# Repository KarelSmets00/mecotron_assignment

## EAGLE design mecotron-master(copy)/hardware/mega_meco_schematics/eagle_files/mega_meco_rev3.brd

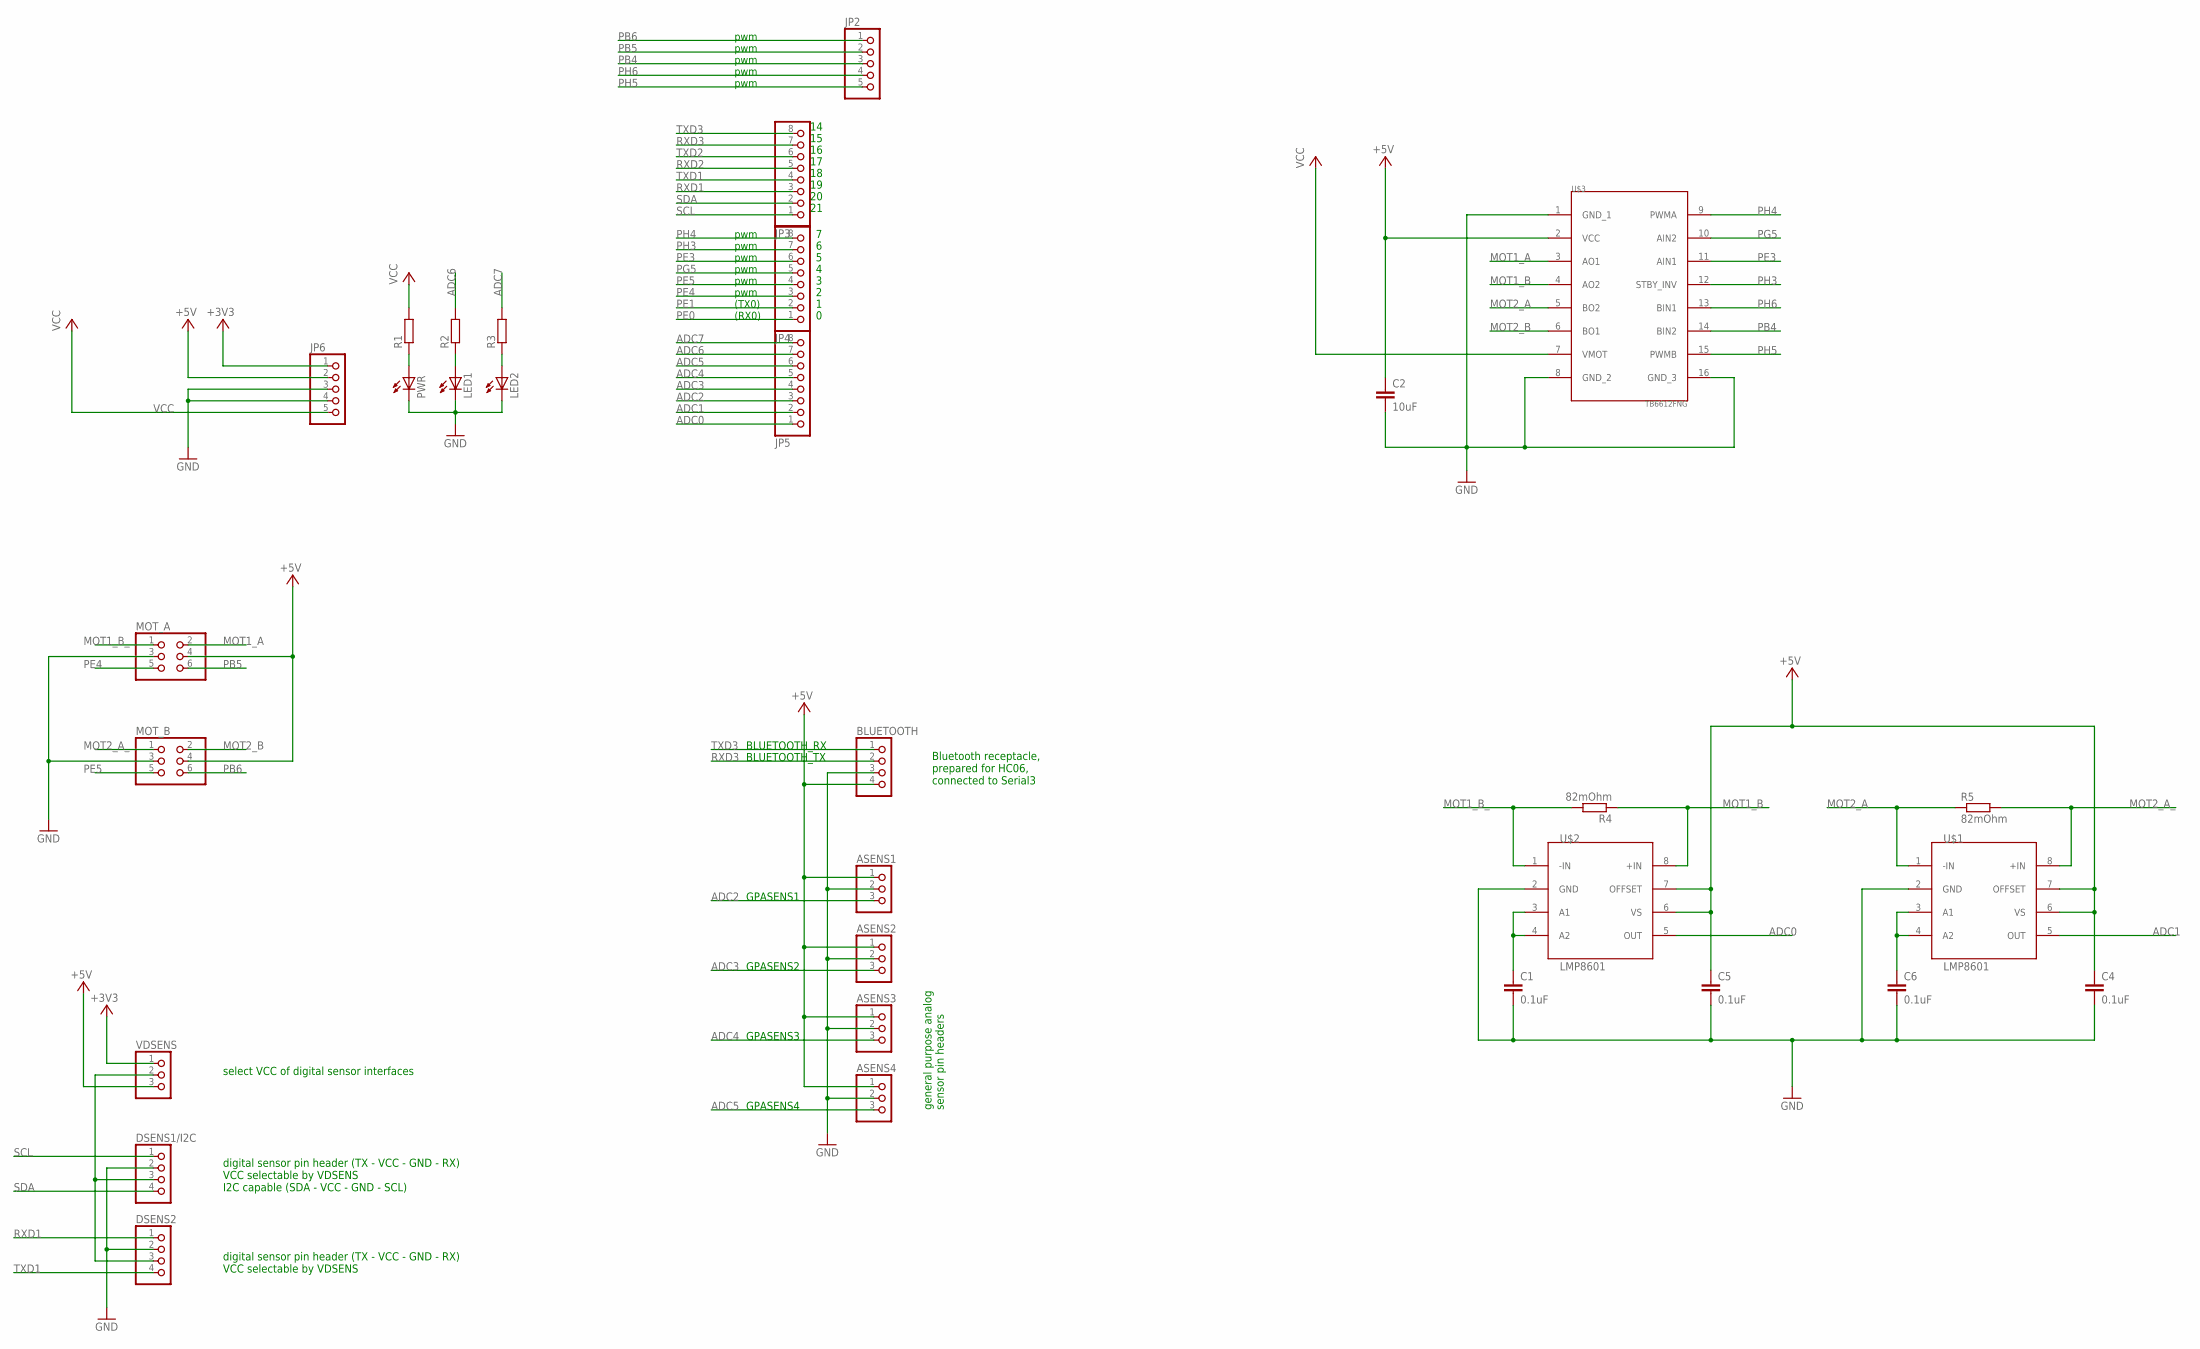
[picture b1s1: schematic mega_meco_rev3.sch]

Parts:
ASENS1, ASENS2, ASENS3, ASENS4: PINHD-1X3; 1X03
BLUETOOTH: PINHD-1X4; 1X04
C1, C4, C5, C6: 0.1uF; C0805
C2: 10uF; C1206
DSENS1/I2C, DSENS2: PINHD-1X4; 1X04
JP2, JP6: PINHD-1X5; 1X05
JP3, JP4, JP5: PINHD-1X8; 1X08
LED1, LED2: LED3MM
MOT_A: PINHD-2X3; 2X03
MOT_B: PINHD-2X3; 2X03
PWR: LED5MM
R1, R2, R3: R-EU_R0805; R0805
R4, R5: 82mOhm; R1206
U$1, U$2: LMP8601; SOIC127P600X175-8N
U$3: TB6612FNG; TB6612FNG_CARRIER
VDSENS: PINHD-1X3; 1X03

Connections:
+3V3: JP6.1, VDSENS.1
+5V: ASENS1.1, ASENS2.1, ASENS3.1, ASENS4.1, BLUETOOTH.4, C2.1, C4.1, C5.1, JP6.2, MOT_A.4, MOT_B.4, U$1.6 (VS), U$1.7 (OFFSET), U$2.6 (VS), U$2.7 (OFFSET), U$3.2 (VCC), VDSENS.3
ADC0: JP5.1, U$2.5 (OUT)
ADC1: JP5.2, U$1.5 (OUT)
ADC2: ASENS1.3, JP5.3
ADC3: ASENS2.3, JP5.4
ADC4: ASENS3.3, JP5.5
ADC5: ASENS4.3, JP5.6
ADC6: JP5.7, R2.2
ADC7: JP5.8, R3.2
GND: ASENS1.2, ASENS2.2, ASENS3.2, ASENS4.2, BLUETOOTH.3, C1.2, C2.2, C4.2, C5.2, C6.2, DSENS1/I2C.2, DSENS2.2, JP6.3, JP6.4, LED1.K (C), LED2.K (C), MOT_A.3, MOT_B.3, PWR.K (C), U$1.2 (GND), U$2.2 (GND), U$3.1 (GND_1), U$3.8 (GND_2), U$3.16 (GND_3)
MOT1_A: MOT_A.2, U$3.3 (AO1)
MOT1_B: R4.1, U$2.8 (+IN), U$3.4 (AO2)
MOT1_B_: MOT_A.1, R4.2, U$2.1 (-IN)
MOT2_A: R5.1, U$1.1 (-IN), U$3.5 (BO2)
MOT2_A_: MOT_B.1, R5.2, U$1.8 (+IN)
MOT2_B: MOT_B.2, U$3.6 (BO1)
unnamed: PWR.A, R1.1
unnamed: LED1.A, R2.1
unnamed: C1.1, U$2.3 (A1), U$2.4 (A2)
unnamed: C6.1, U$1.3 (A1), U$1.4 (A2)
unnamed: DSENS1/I2C.3, DSENS2.3, VDSENS.2
unnamed: LED2.A, R3.1
PB4: JP2.3, U$3.14 (BIN2)
PB5: JP2.2, MOT_A.6
PB6: JP2.1, MOT_B.6
PE0: JP4.1
PE1: JP4.2
PE3: JP4.6, U$3.11 (AIN1)
PE4: JP4.3, MOT_A.5
PE5: JP4.4, MOT_B.5
PG5: JP4.5, U$3.10 (AIN2)
PH3: JP4.7, U$3.12 (STBY_INV)
PH4: JP4.8, U$3.9 (PWMA)
PH5: JP2.5, U$3.15 (PWMB)
PH6: JP2.4, U$3.13 (BIN1)
RXD1: DSENS2.1, JP3.3
RXD2: JP3.5
RXD3: BLUETOOTH.2, JP3.7
SCL: DSENS1/I2C.1, JP3.1
SDA: DSENS1/I2C.4, JP3.2
TXD1: DSENS2.4, JP3.4
TXD2: JP3.6
TXD3: BLUETOOTH.1, JP3.8
VCC: JP6.5, R1.2, U$3.7 (VMOT)

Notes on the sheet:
pwm
(TX0)
(RX0)
BLUETOOTH_RX
BLUETOOTH_TX
GPASENS1
GPASENS2
GPASENS3
Bluetooth receptacle, prepared for HC06, connected to Serial3
digital sensor pin header (TX - VCC - GND - RX) VCC selectable by VDSENS I2C capable (SDA - VCC - GND - SCL)
GPASENS4
general purpose analog sensor pin headers
digital sensor pin header (TX - VCC - GND - RX) VCC selectable by VDSENS
select VCC of digital sensor interfaces

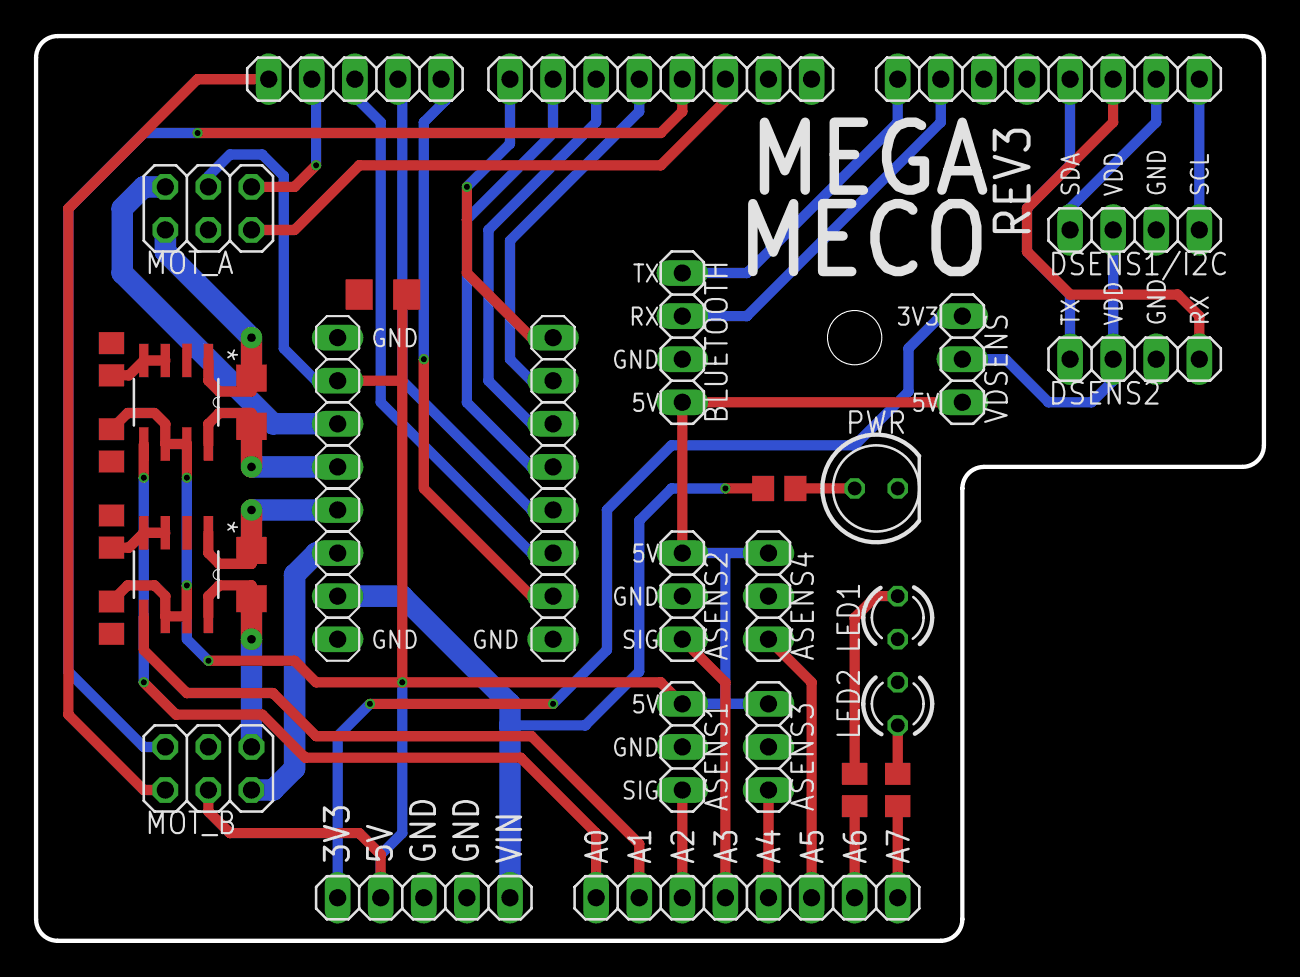
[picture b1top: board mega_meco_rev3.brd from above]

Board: 2 copper layers, 72.4 x 53.3 mm, 31 parts (0 on the bottom side), 41 nets.

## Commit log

2021-10-25 toevoeging mecotron repository
2021-10-25 cleaned up repo
2021-10-25 toevoeging readme en gitignore
2021-11-06 screenshot van kleine afleiding continu model dc-motor
2021-11-06 added intro OZ files
2021-11-06 testjeeee
2021-11-10 cheatsheet for ease of use
2021-11-10 added withboard from assignement brainstorm
2021-11-10 arduino working directory in git
2021-11-10 measurements of stepinput, MotorA
2021-11-10 file voor identificatie aangemaakt (matlab)
2021-11-10 tweede set aan data
2021-11-10 derde set aan data
2021-11-10 data singlestep
2021-11-10 matlab 1e model geidentificeerd (uitgebreid model)
2021-11-10 uitbreinding identificatie file naar positie model
2021-11-12 ppt for FB1
2021-11-12 ppt update
2021-11-12 matlab file for periodic data identification
2021-11-12 niets speciaals
2021-11-13 data locatie mathias toegevoegd
2021-11-13 2e orde systeem, 5e orde systeem met filtering, en mogelijkheid tot het gebruik van andere spanningen is toegevoegd
2021-11-16 added model 3th order 2 zeros
2021-11-16 StepInput measuremtents with cart
2021-11-16 comparing models plus checking coverage
2021-11-16 started linearity check
2021-11-17 aanpassingen aan model_identification + modelcoverage
2021-11-17 lin check file update
2021-11-17 added path names to run on every pc, splitted data preproc flile, renamed meanBackup to mean_
2021-11-18 nieuwe data plus code toegevoegd
2021-11-18 lineariteit wordt nu ook vergelijken met 12V
2021-11-19 disturbance identification try
2021-11-20 kleine aanpassing in model_identification cart
2021-11-20 current measurments visualised
2021-11-20 added figure
2021-11-20 added output save, seperated position model calculations in seperate file, universalized data input
2021-11-20 fixed bugs in prevous changes
2021-11-20 calculated angular speed and plotted against current in current measurement experiment
2021-11-20 afgesproken taken van op vrijdag19/11 zijn uitgevoerd
2021-11-20 bode plots were deleted once more after the merging error
2021-11-22 start assignement 2, designed PI, PID = work in progress
2021-11-22 tutorial PID added for testing different controllers
2021-11-22 tried PM=65 and 75, added flexibility for Kp, Ki, and Kd in Qrobotics
2021-11-23 filter gefixt
2021-11-27 plots added
2021-11-27 made PILead file, changed PI PM
2021-11-27 kleine aanpassingen en plots
2021-11-27 fixed identification files na aanpassingen van mathias, extra file voor plots, niewe model file voor gefinterde motor model
2021-11-27 corrected some model saving issues
2021-11-27 generated 3a figs
2021-11-27 made plots voor 3b, nog cart model save files bijgevoegd en data_preprosessing_cart file gearchiveerd
2021-11-29 data from PI controller
2021-11-29 new PI controller implemented
2021-12-02 further docs and measurements assignement 2
2021-12-03 made I controller file and worked on PI
2021-12-03 reloaded model files of assignement 1
2021-12-03 Kalmanfilter downloaded
2021-12-07 Work in progress position controller
2021-12-07 vraag_2d , not right at the moment
2021-12-08 K and Q tuning
2021-12-08 vraag 2d werkend
2021-12-08 data voor assignment 3 plus nog wat arduino scriptjes
2021-12-08 added oz5 kalmanexperiment file voor nis snis
2021-12-10 data impor function voor assig3ce
2021-12-10 2 bestanden verwijderd
2021-12-10 NIS en SNIS aangemaakt
2021-12-10 plots for questions 3C and 3E
2021-12-10 NIS SNIS bijgewerkt en geautomatiseerd
2021-12-10 files opgeschoond
2021-12-10 pached data import to only hold back csv files
2021-12-11 some small modifications to plots
2021-12-11 nieuwe metingen voor Ktuning en Q=1e-8
2021-12-11 kleine aanpassing ivm paramater vraag b rechtgezet
2021-12-12 reran nis snis na Qe_8 file binnengekomen was
2021-12-15 made file for excersise 2c
2021-12-15 QR optimalisation for assignment 5
2021-12-15 extra meting voor Q=5e-7
2021-12-16 meting voor confidence intervals
2021-12-16 moved assignement 4 to 5
2021-12-17 swivle assignment 5 met simultanuous control
2021-12-17 foutje in de A-matrix gefixt, hopelijk
2021-12-18 added autogen plot file voor 3e fixed plots voor 3f en upgraded data preprosessing function van assignement 3. Ook nieuwe backup van de tex van het verslag
2021-12-18 updates on assign 1 and a few on 2
2021-12-18 corrected I_controller design script
2021-12-19 made figs for the I coltroller (open loop closed loop and step rp adapted file for I controller to auto store figs and name them to used PM backed up main.tex in file in this repo
2021-12-20 preparation videos
2021-12-20 nog aanpassingen voor verslag
2021-12-21 vanalle matlab na de mp4 uit comit te moeten halen
2021-12-22 poging tot tuning
2021-12-22 nieuwe data 22/12
2021-12-22 file aangepast
2021-12-22 arduino files van assign 5 in mapje old geplaatst
2021-12-22 werk namiddag 22 12
2021-12-22 confidence intervals
2021-12-22 data 22 12
2021-12-22 plotjes veel plotjes
2021-12-23 corrected assignments and video
2021-12-23 final plots verslag
2021-12-23 compleetheid check assignement
2021-12-23 code gezipt
2021-12-23 reports in indienen folder
